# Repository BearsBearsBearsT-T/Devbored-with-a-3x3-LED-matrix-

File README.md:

**Devbored RP2040**

I finally finished my first PCB! It’s a Devboard using the RP2040 chip. It was more compliated than I thought it would be, but I got it working and learned alot from it. I wanted to learn how to make a PCB but I often get bored when I am not intrusted in the project or it feels too 'beginner' so i decided to jump in the middle end of the pool and make a Devbored!!

This project is a custom RP2040 Devboard. It’s a 2-layer PCB designed in KiCad that breaks out the pins for the RP2040 chip and includes all the necessary parts like the crystal, power whires, and a USB-C port.

**Pictures:**

**BOM for PCB:**

[DevboredBOM.csv](https://github.com/user-attachments/files/27150701/DevboredBOM.csv)
Reference	Value	Datasheet	Footprint	Qty	DNP

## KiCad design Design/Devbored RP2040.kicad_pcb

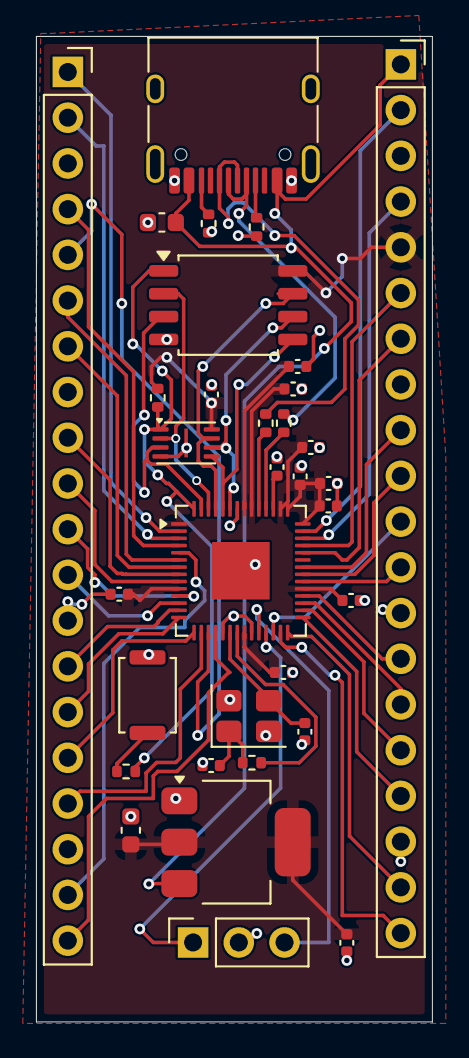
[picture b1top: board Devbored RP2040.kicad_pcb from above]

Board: 2 copper layers, 22.0 x 54.8 mm, 33 parts (0 on the bottom side), 52 nets.

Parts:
C1, C2, C5, C6, C7, C8, C9, C11, C17: 0.1uf; C_0402_1005Metric
C10, C12, C26: 1uf; C_0402_1005Metric
C13, C14: 10uf; C_0603_1608Metric
C15, C16: 15pf; C_0402_1005Metric
J1: USB_C_Receptacle_USB2.0_14P; USB_C_Receptacle_HRO_TYPE-C-31-M-12
J2, J3: Conn_01x20_Pin; PinSocket_1x20_P2.54mm_Vertical
J4: Conn_01x03_Pin; PinSocket_1x03_P2.54mm_Vertical
R1, R2: 5.1k; R_0402_1005Metric
R3, R4: 27om; R_0402_1005Metric
R5, R18: 1k; R_0402_1005Metric
R6: 10k; R_0402_1005Metric
SW1: SW_Push; SW_Push_SPST_NO_Alps_SKRK
U1: RP2040; QFN-56-1EP_7x7mm_P0.4mm_EP3.2x3.2mm
U2: NCP1117-1.5_SOT223; SOT-223-3_TabPin2
U3: W25Q128JVS; SOIC-8_5.3x5.3mm_P1.27mm
U4: APS1604M-3SQRx-ZR; Winbond_USON-8-1EP_3x2mm_P0.5mm_EP0.2x1.6mm
Y1: 12 MHz; Crystal_SMD_3225-4Pin_3.2x2.5mm

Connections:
+3V3: C1.1, C2.1, C5.1, C6.1, C7.1, C8.1, C9.1, C10.1, C11.1, C12.1, C13.1, C17.1, J3.5, R6.1, U1.1 (IOVDD), U1.10 (IOVDD), U1.22 (IOVDD), U1.33 (IOVDD), U1.42 (IOVDD), U1.43 (ADC_AVDD), U1.44 (VREG_VIN), U1.48 (USB_VDD), U1.49 (IOVDD), U2.2 (VO), U3.8 (VCC), U4.8 (VDD)
GND: C1.2, C2.2, C5.2, C6.2, C7.2, C8.2, C9.2, C10.2, C11.2, C12.2, C13.2, C14.2, C15.2, C16.2, C17.2, C26.1, J1.A1 (GND), J1.A12 (GND), J1.B1 (GND), J1.B12 (GND), J1.SH (SHIELD), J2.3, J2.8, J2.13, J2.18, J3.3, J3.8, J3.13, J3.18, J4.2, R1.2, R2.2, SW1.1, U1.19 (TESTEN), U1.23 (DVDD), U1.50 (DVDD), U1.57 (GND), U2.1 (GND), U3.4 (GND), U4.4 (VSS), U4.9 (EPAD), Y1.2 (G), Y1.4 (G)
GPIO0: J2.1, U1.2 (GPIO0)
GPIO1: J2.2, U1.3 (GPIO1)
GPIO2: J2.4, U1.4 (GPIO2)
GPIO3: J2.5, U1.17 (GPIO14)
GPIO4: J2.6, U1.6 (GPIO4)
GPIO5: J2.7, U1.7 (GPIO5)
GPIO6: J2.9, U1.8 (GPIO6)
GPIO7: J2.10, U1.9 (GPIO7)
GPIO8: J2.11, U1.11 (GPIO8)
GPIO9: J2.12, U1.12 (GPIO9)
GPIO10: J2.14, U1.13 (GPIO10)
GPIO11: J2.15, U1.14 (GPIO11)
GPIO12: J2.16, U1.15 (GPIO12)
GPIO13: J2.17, U1.16 (GPIO13)
GPIO14: J2.19, U1.5 (GPIO3)
GPIO15: J2.20, U1.18 (GPIO15)
GPIO16: J3.20, U1.27 (GPIO16)
GPIO17: J3.19, U1.28 (GPIO17)
GPIO18: J3.17, U1.29 (GPIO18)
GPIO19: J3.16, U1.30 (GPIO19)
GPIO20: J3.15, U1.31 (GPIO20)
GPIO21: J3.14, U1.32 (GPIO21)
GPIO22: J3.12, U1.34 (GPIO22)
GPIO23: J3.10, U1.35 (GPIO23)
GPIO24: J3.9, U1.36 (GPIO24)
GPIO26_ADC0: J3.7, U1.38 (GPIO26/ADC0)
GPIO27_ADC1: J3.6, U1.39 (GPIO27/ADC1)
GPIO28_ADC2: J3.4, U1.40 (GPIO28/ADC2)
GPIO29_ADC3: J3.2, U1.41 (GPIO29/ADC3)
unnamed: C15.1, R5.2, Y1.1
unnamed: J1.A5 (CC1), R1.1
unnamed: J1.B5 (CC2), R2.1
unnamed: R18.1, SW1.2
unnamed: R3.2, U1.46 (USB_DM)
unnamed: R4.2, U1.47 (USB_DP)
unnamed: C26.2, U1.45 (VREG_VOUT)
QSPI_SCLK: U1.51 (QSPI_SD3), U3.6 (CLK), U4.6 (SCLK)
QSPI_SD0: U1.52 (QSPI_SCLK), U3.5 (DI/IO_{0}), U4.5 (SI/SIO0)
QSPI_SD1: U1.54 (QSPI_SD2), U3.2 (DO/IO_{1}), U4.2 (SO/SIO1)
QSPI_SD2: U1.55 (QSPI_SD1), U3.3 (~WP/IO_{2}), U4.3 (SIO2)
QSPI_SD3: U1.53 (QSPI_SD0), U3.7 (~HOLD/~RESET/IO_{3}), U4.7 (SIO3)
QSPI_SS: R6.2, R18.2, U1.56 (~QSPI_SS), U3.1 (~CS), U4.1 (~CE)
RUN: J3.11, U1.26 (RUN)
SWCLK: J4.3, U1.24 (SWCLK)
SWIDO: J4.1, U1.25 (SWDIO)
USB_D+: J1.A6 (D+), J1.B6 (D+), R4.1
USB_D-: J1.A7 (D-), J1.B7 (D-), R3.1
VBUS: C14.1, J1.A4 (VBUS), J1.A9 (VBUS), J1.B4 (VBUS), J1.B9 (VBUS), J3.1, U2.3 (VI)
XIN: C16.1, U1.20 (XIN), Y1.3
XOUT: R5.1, U1.21 (XOUT)

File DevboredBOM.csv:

Reference	Value	Datasheet	Footprint	Qty	DNP
C1,C2,C3,C4,C5,C6,C7,C8,C9,C11,C17	0.1uf		Capacitor_SMD:C_0402_1005Metric	11	
C10,C12	1uf		Capacitor_SMD:C_0402_1005Metric	2	
C13,C14	10uf		Capacitor_SMD:C_0603_1608Metric	2	
C15,C16	15pf		Capacitor_SMD:C_0402_1005Metric	2	
C18	C			1	
C26	1uf		C_0402_1005Metric	1	
C29	1uf			1	
J1	USB_C_Receptacle_USB2.0_14P	https://www.usb.org/sites/default/files/documents/usb_type-c.zip	Connector_USB:USB_C_Receptacle_HRO_TYPE-C-31-M-12	1	
J2,J3	Conn_01x20_Pin		Connector_PinSocket_2.54mm:PinSocket_1x20_P2.54mm_Vertical	2	
J4	Conn_01x03_Pin		Connector_PinSocket_2.54mm:PinSocket_1x03_P2.54mm_Vertical	1	
R1,R2	5.1k		Resistor_SMD:R_0402_1005Metric	2	
R3,R4	27om		Resistor_SMD:R_0402_1005Metric	2	
R5,R18	1k		Resistor_SMD:R_0402_1005Metric	2	
R6	10k		Resistor_SMD:R_0402_1005Metric	1	
SW1	SW_Push		Button_Switch_SMD:SW_Push_SPST_NO_Alps_SKRK	1	
U1	RP2040	https://datasheets.raspberrypi.com/rp2040/rp2040-datasheet.pdf	Package_DFN_QFN:QFN-56-1EP_7x7mm_P0.4mm_EP3.2x3.2mm	1	
U2	NCP1117-1.5_SOT223	http://www.onsemi.com/pub_link/Collateral/NCP1117-D.PDF	Package_TO_SOT_SMD:SOT-223-3_TabPin2	1	
U3	W25Q128JVS	https://www.winbond.com/resource-files/w25q128jv_dtr%20revc%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	Package_SO:SOIC-8_5.3x5.3mm_P1.27mm	1	
U4	APS1604M-3SQRx-ZR	https://www.mouser.com/datasheet/2/1127/APM_PSRAM_QSPI_APS16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	Package_SON:Winbond_USON-8-1EP_3x2mm_P0.5mm_EP0.2x1.6mm	1	
Y1	12 MHz		Crystal:Crystal_SMD_3225-4Pin_3.2x2.5mm	1

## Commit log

2026-04-22 Rename report file to DevboredRP2040.txt
2026-04-24 Add README for Devbored RP2040 project
    Added a README file detailing the Devbored RP2040 project, including struggles faced during development.
2026-04-27 Revise README with detailed project description
    Expanded project description and added details about the PCB design and challenges faced during the build process.
2026-04-28 Rename Devbored RP2040.kicad_pcb to Design/Devbored RP2040.kicad_pcb
    adding folder
2026-04-28 Rename Devbored RP2040.kicad_pro to Design/Devbored RP2040.kicad_pro
2026-04-28 Rename Devbored RP2040.kicad_sch to Design/Devbored RP2040.kicad_sch
2026-04-28 Rename report for Devbored att1.txt to report for RP2040 Devbored.txt
2026-04-28 Rename .step to .Devbored.step
2026-04-28 Rename Devbored.step to Devbored.stp
2026-05-02 Update README with more images
    Added additional screenshots to the README.
2026-05-02 Cleanup component list in README.md
    Removed detailed component list from README.
2026-05-02 Remove error message and add new screenshot
2026-05-12 Rename ABX00162-cad-files.zip to gerber-files.zip
2026-05-13 Rename Devbored_RP2040p.kicad_sch to Design/Devbored_RP2040p.kicad_sch
2026-05-13 Rename Devbored RP2040p.kicad_pcb to Design/Devbored RP2040p.kicad_pcb
2026-05-13 Rename ABX00162-cad-files (1).zip to Dev.RP2040-cad-files (1).zip
